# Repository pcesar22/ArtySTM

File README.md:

# ArtySTM
Artix 7 FPGA + STM32F4 Micro Board development

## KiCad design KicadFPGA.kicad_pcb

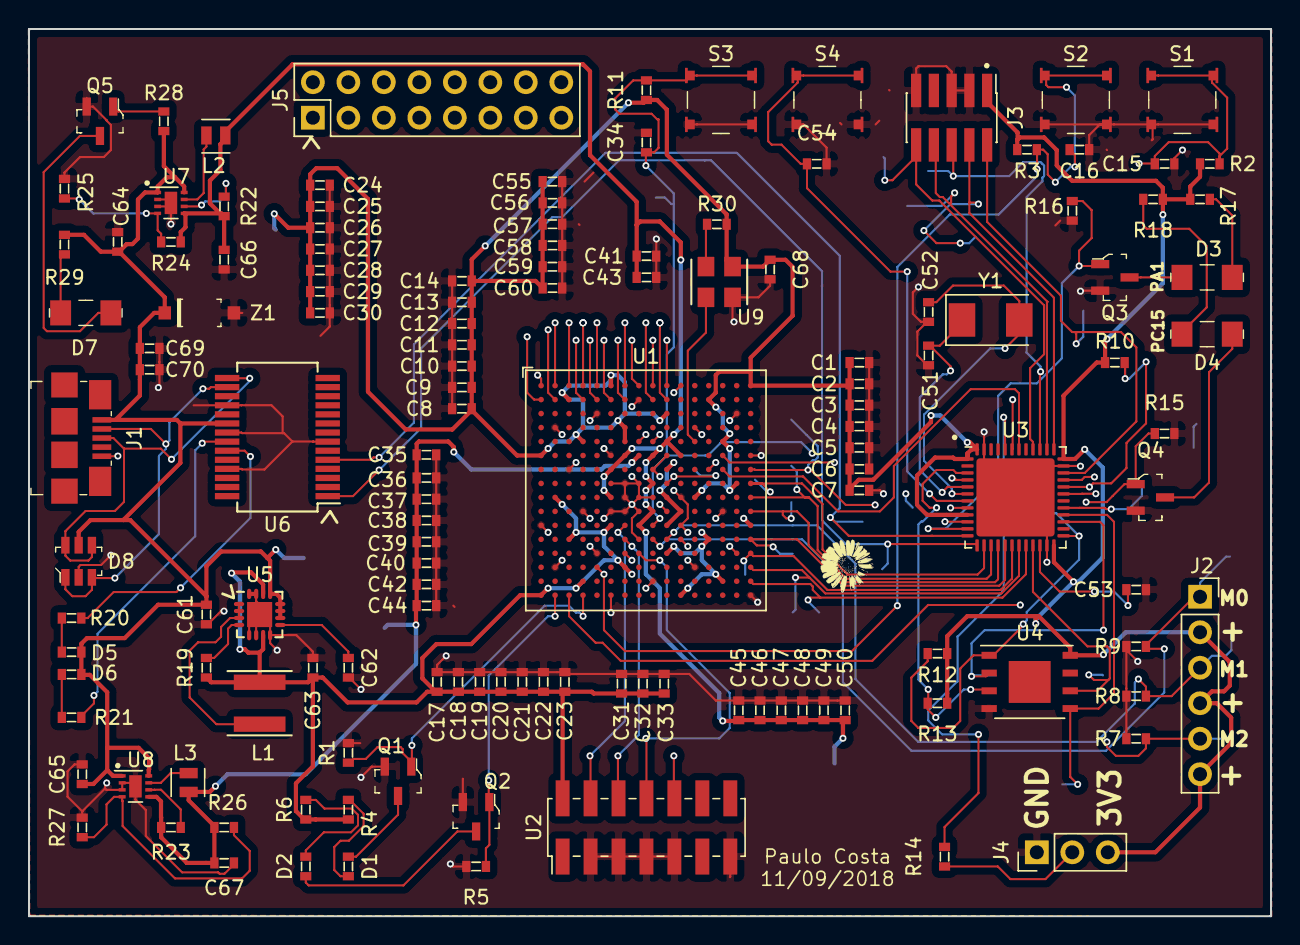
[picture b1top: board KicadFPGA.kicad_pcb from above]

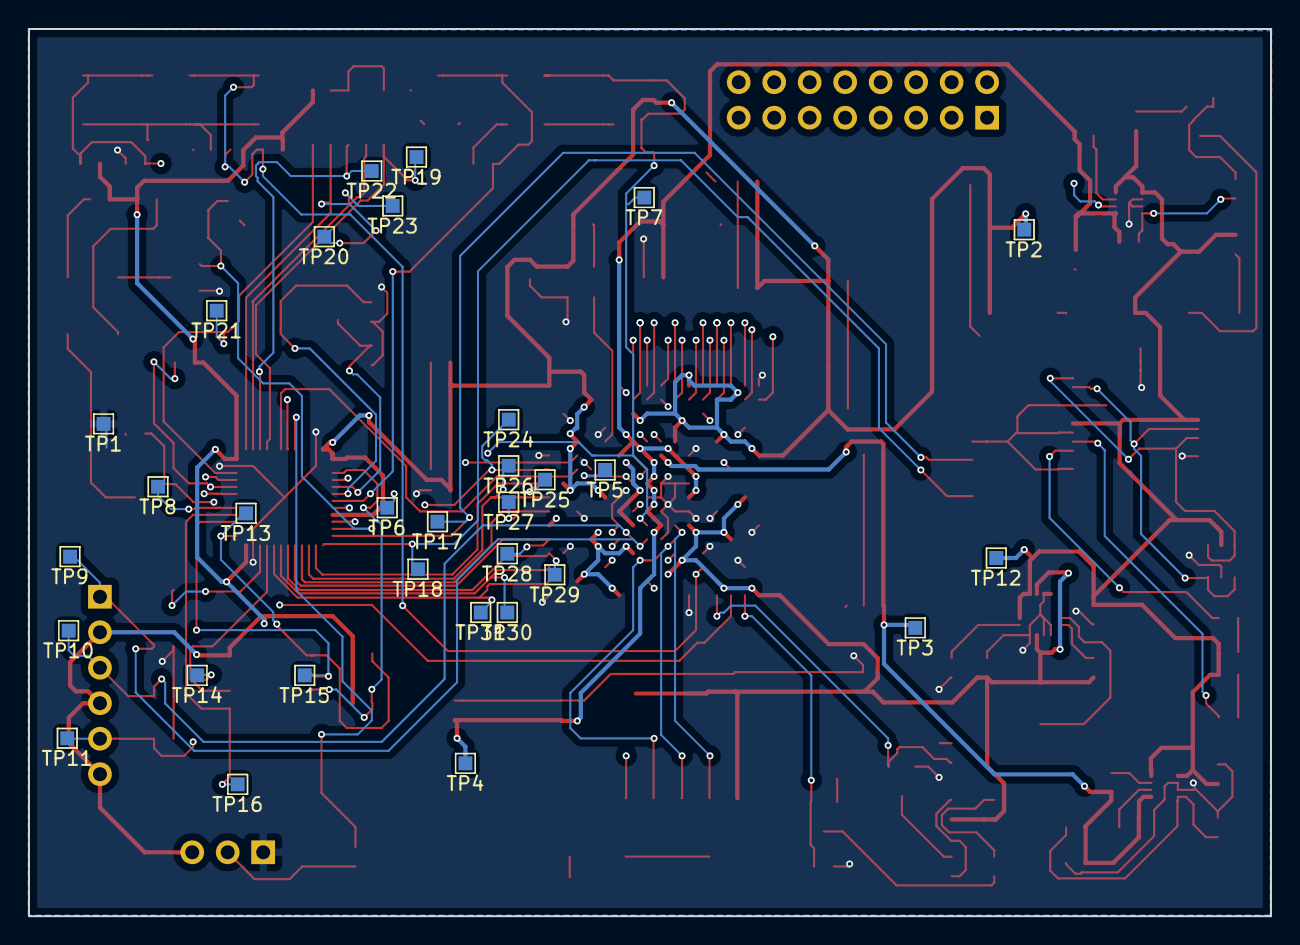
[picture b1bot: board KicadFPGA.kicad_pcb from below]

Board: 4 copper layers, 88.9 x 63.5 mm, 167 parts (31 on the bottom side), 94 nets.

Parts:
C1, C8, C17, C24, C41: 47uF; 0603
C2, C3, C9, C10, C18, C19, C25, C26, C32, C35, C36, C37, C46, C47, C53, C58, C59, C60, C69: 4.7uF; 0603
C4, C5, C6, C7, C11, C12, C13, C14, C20, C21, C22, C23, C27, C28, C29, C30, C43, C48, C49, C50: 0.47uF; 0603
C15, C16, C34, C54, C55, C56, C57, C68, C70: 0.1uF; 0603
C31, C42, C44: 47nF; 0603
C33, C38, C39, C40: 470nF; 0603
C45: 100uF; 0603
C51, C52: 8pF; 0603
C61, C64, C65: 10uF; 0603
C62: 390pF; 0603
C63, C66, C67: 22uF; 0603
D1, D2: GREEN; 0603
D3: BLUE; 1206
D4, D7: RED; 1206
D5: LED_RX; 0603
D6: LED_TX; 0603
D8: USBLC6-4SC6; SOT23-6L
J1: USB_B_Micro; USB_Micro_B_Female_10118192
J2: Conn_01x06_Male; PinSocket_1x06_P2.54mm_Vertical
J3: Conn_ARM_JTAG_SWD_10; PinHeader_2x05_P1.27mm_Vertical_SMD
J4: Conn_01x03_Male; PinHeader_1x03_P2.54mm_Vertical
J5: Conn_01x16_Male; PinHeader_2x08_P2.54mm_Vertical
L1: 2.2uH; PA4332
L2, L3: 1.0uH; L_TDK_VLF252015MT
Q1, Q2, Q3, Q4, Q5: FDV301N; SOT-23-3
R1, R5, R14, R15, R16, R28: 10k; 0603
R2, R3, R12, R13: 4.7k; 0603
R4, R6, R17, R18, R29: 680; 0603
R7, R8, R9, R30: 1k; 0603
R10, R11, R20, R21: 2.2k; 0603
R19: 100k; 0603
R22, R23: 178k; 0603
R24: 47.5k; 0603
R25, R27: 39.2k; 0603
R26: 118k; 0603
S1, S2, S3, S4: TL3315NF160Q; Switch_Tactile_SMD_4.5x4.5mm_TL3315NF160Q
TP1: tGND; TestPoint_Pad_1.0x1.0mm
TP2: t3V3; TestPoint_Pad_1.0x1.0mm
TP3: t1V8; TestPoint_Pad_1.0x1.0mm
TP4: t1V0; TestPoint_Pad_1.0x1.0mm
TP5: tFPGA_DONE; TestPoint_Pad_1.0x1.0mm
TP6: tFPGA_INIT; TestPoint_Pad_1.0x1.0mm
TP7: tFPGA_PROGRAM; TestPoint_Pad_1.0x1.0mm
TP8: tFPGA_CCLK; TestPoint_Pad_1.0x1.0mm
TP9: tFPGA_M0; TestPoint_Pad_1.0x1.0mm
TP10: tFPGA_M1; TestPoint_Pad_1.0x1.0mm
TP11: tFPGA_M2; TestPoint_Pad_1.0x1.0mm
TP12: t5V; TestPoint_Pad_1.0x1.0mm
TP13: tSPI_CS; TestPoint_Pad_1.0x1.0mm
TP14: tSPI_SCK; TestPoint_Pad_1.0x1.0mm
TP15: tSPI_MISO; TestPoint_Pad_1.0x1.0mm
TP16: tSPI_MOSI; TestPoint_Pad_1.0x1.0mm
TP17: tRXI; TestPoint_Pad_1.0x1.0mm
TP18: tTXO; TestPoint_Pad_1.0x1.0mm
TP19: tJTAG_RST; TestPoint_Pad_1.0x1.0mm
TP20: tJTAG_TCK; TestPoint_Pad_1.0x1.0mm
TP21: tJTAG_TMS; TestPoint_Pad_1.0x1.0mm
TP22: tJTAG_TDO; TestPoint_Pad_1.0x1.0mm
TP23: tJTAG_TDI; TestPoint_Pad_1.0x1.0mm
TP24: tBUS0; TestPoint_Pad_1.0x1.0mm
TP25: tBUS1; TestPoint_Pad_1.0x1.0mm
TP26: tBUS2; TestPoint_Pad_1.0x1.0mm
TP27: tBUS3; TestPoint_Pad_1.0x1.0mm
TP28: tBUS4; TestPoint_Pad_1.0x1.0mm
TP29: tBUS5; TestPoint_Pad_1.0x1.0mm
TP30: tBUS6; TestPoint_Pad_1.0x1.0mm
TP31: tBUS7; TestPoint_Pad_1.0x1.0mm
U1: XC7A35T-FTG256; BGA-256_17.0x17.0mm_Layout16x16_P1.0mm_Ball0.5mm_Pad0.4mm_N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
U2: Xilinx_FPGA_JTAG_Conn_2x7; PinHeader_2x07_P2.00mm_Vertical_SMD
U3: STM32F411CEUx; QFN-48-1EP_7x7mm_P0.5mm_EP5.6x5.6mm
U4: MT25QU128; DFN-8-1EP_6x5mm_P1.27mm_EP3x3mm
U5: TPS62142; QFN-16-1EP_3x3mm_P0.5mm_EP1.8x1.8mm
U6: FT232RL; SSOP-28_5.3x10.2mm_P0.65mm
U7, U8: TLV62084ADSGx; WSON-8-1EP_2x2mm_P0.5mm_EP0.9x1.6mm
U9: SiT8008B; SiT8008B_3.2x2.5MM
Y1: 25MHz; Crystal_SMD_Abracon_ABM3-2Pin_5.0x3.2mm
Z1: MMSZ5231B-7-F; SOD-123

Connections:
+1V0: C41.1, C43.1, C45.1, C46.1, C47.1, C48.1, C49.1, C50.1, C66.1, L2.1, R22.1, R24.1, TP4.1, U1.E10, U1.F7, U1.F9, U1.F11, U1.G6, U1.H9, U1.J6, U1.K9, U1.L8, U7.5
+1V8: C35.1, C36.1, C37.1, C38.1, C39.1, C40.1, C42.1, C44.1, C67.1, L3.1, R23.1, R26.1, TP3.1, U1.F8, U1.G10, U1.J10, U1.K11, U1.L10, U8.5
+3V3: C1.1, C2.1, C3.1, C4.1, C5.1, C6.1, C7.1, C8.1, C9.1, C10.1, C11.1, C12.1, C13.1, C14.1, C17.1, C18.1, C19.1, C20.1, C21.1, C22.1, C23.1, C24.1, C25.1, C26.1, C27.1, C28.1, C29.1, C30.1, C31.1, C32.1, C33.1, C55.1, C56.1, C57.1, C58.1, C59.1, C60.1, C63.1, C68.1, J2.2, J2.4, J2.6, J3.1, J4.3, L1.2, R2.1, R3.1, R4.1, R6.1, R10.1, R11.1, R12.1, R13.1, R17.1, R18.1, R19.1, R30.1, TP2.1, U1.A6, U1.A16, U1.B3, U1.B13, U1.C10, U1.D7, U1.E4, U1.E7, U1.E14, U1.F1, U1.H15, U1.J2, U1.J12, U1.L6, U1.L16, U1.M3, U1.M13, U1.N10, U1.P7, U1.R4, U1.R14, U1.T1, U1.T11, U2.2, U3.1, U3.9, U3.24, U3.36, U3.48, U4.8, U5.7, U5.14, U9.1
+5V: C61.1, C64.1, C65.1, C69.1, C70.1, D5.2, D6.2, D8.5, J1.1, R28.1, R29.1, TP12.1, U5.10, U5.11, U5.12, U5.13, U6.20, U7.1, U7.8, U8.1, U8.8, Z1.K
/Arty Bank 14, 15/CLK_100MHZ: U1.E12, U9.3
BOOT0: R14.2, U3.44
BREAK0: J5.1, U1.B1
BREAK1: J5.2, U1.B2
BREAK2: J5.3, U1.A2
BREAK3: J5.4, U1.A3
BREAK4: J5.5, U1.B4
BREAK5: J5.6, U1.A4
BREAK6: J5.7, U1.B5
BREAK7: J5.8, U1.A5
BREAK8: J5.9, U1.B6
BREAK9: J5.10, U1.B7
BREAK10: J5.11, U1.A7
BREAK11: J5.12, U1.A8
BREAK12: J5.13, U1.B9
BREAK13: J5.14, U1.A9
BREAK14: J5.15, U1.B10
BREAK15: J5.16, U1.A10
BUS0: TP24.1, U1.G16, U3.10
BUS1: TP25.1, U1.H16, U3.14
BUS2: TP26.1, U1.J16, U3.15
BUS3: TP27.1, U1.K16, U3.16
BUS4: TP28.1, U1.M16, U3.17
BUS5: TP29.1, U1.N16, U3.18
BUS6: TP30.1, U1.P16, U3.19
BUS7: TP31.1, U1.R16, U3.20
D+: D8.4, D8.6, J1.3, U6.15
D-: D8.1, D8.3, J1.2, U6.16
FLASH_W: R13.2, U3.3, U4.3
FPGA_BUTTON_1: C15.1, R2.2, S1.1, S1.2, U1.T3
FPGA_BUTTON_2: C16.1, R3.2, S2.1, S2.2, U1.P5
FPGA_CCLK: TP8.1, U1.E8, U3.29
FPGA_DONE: TP5.1, U1.H10, U3.33
FPGA_INIT_B: R10.2, TP6.1, U1.K10, U3.32
FPGA_LED_1: Q2.1, R5.1, U1.T2
FPGA_LED_2: Q1.1, R1.1, U1.T4
FPGA_PROGRAM_B: C34.1, R11.2, S3.1, S3.2, TP7.1, U1.L9, U3.31
FT232_RXI: TP17.1, U3.12, U6.5
FT232_TXO: TP18.1, U3.13, U6.1
GND: C1.2, C2.2, C3.2, C4.2, C5.2, C6.2, C7.2, C8.2, C9.2, C10.2, C11.2, C12.2, C13.2, C14.2, C15.2, C16.2, C17.2, C18.2, C19.2, C20.2, C21.2, C22.2, C23.2, C24.2, C25.2, C26.2, C27.2, C28.2, C29.2, C30.2, C31.2, C32.2, C33.2, C34.2, C35.2, C36.2, C37.2, C38.2, C39.2, C40.2, C41.2, C42.2, C43.2, C44.2, C45.2, C46.2, C47.2, C48.2, C49.2, C50.2, C51.2, C52.2, C53.2, C54.2, C55.2, C56.2, C57.2, C58.2, C59.2, C60.2, C61.2, C62.2, C63.2, C64.2, C65.2, C66.2, C67.2, C68.2, C69.2, C70.2, D8.2, J1.5, J3.3, J3.5, J3.9, J4.1, Q1.2, Q2.2, Q3.2, Q4.2, Q5.2, R1.2, R5.2, R7.1, R8.1, R9.1, R15.2, R16.2, R25.2, R27.2, S1.3, S1.4, S2.3, S2.4, S3.3, S3.4, S4.3, S4.4, TP1.1, U1.A1, U1.A11, U1.B8, U1.C5, U1.C15, U1.D2, U1.D12, U1.E9, U1.F6, U1.F10, U1.F16, U1.G3, U1.G9, U1.G13, U1.H6, U1.H7, U1.H8, U1.J7, U1.J8, U1.J9, U1.J11, U1.K4, U1.K6, U1.K7, U1.K8, U1.K14, U1.L1, U1.L11, U1.M8, U1.N5, U1.N15, U1.P2, U1.P12, U1.R9, U1.T6, U1.T16, U2.3, U2.5, U2.7, U2.9, U2.13, U3.8, U3.23, U3.35, U3.47, U3.49, U4.4, U5.5, U5.6, U5.8, U5.15, U5.16, U5.17, U6.7, U6.18, U6.21, U6.25, U7.2, U7.3, U7.9, U8.2, U8.3, U8.9, U9.2, Z1.A
I2C_SCL: U1.G14, U3.42
I2C_SDA: U1.F14, U3.43
M0_0: J2.1, R9.2, TP9.1, U1.M9
M1_0: J2.3, R8.2, TP10.1, U1.M10
M2_0: J2.5, R7.2, TP11.1, U1.M11
NRST: C54.1, S4.1, S4.2, U3.7
unnamed: C51.1, U3.5, Y1.1
unnamed: C52.1, U3.6, Y1.2
unnamed: C62.1, U5.9
unnamed: D1.1, Q1.3
unnamed: D1.2, R4.2
unnamed: D2.1, Q2.3
unnamed: D2.2, R6.2
unnamed: D3.1, Q3.3
unnamed: D3.2, R17.2
unnamed: D4.1, Q4.3
unnamed: D4.2, R18.2
unnamed: D5.1, R20.1
unnamed: D6.1, R21.1
unnamed: D7.1, Q5.3
unnamed: D7.2, R29.2
unnamed: J4.2, R14.1
unnamed: L1.1, U5.1, U5.2, U5.3
unnamed: L2.2, U7.7
unnamed: L3.2, U8.7
unnamed: Q5.1, R28.2
unnamed: R19.2, U5.4
unnamed: R20.2, U6.23
unnamed: R21.2, U6.22
unnamed: R22.2, U7.6
unnamed: R23.2, U8.6
unnamed: R24.2, R25.1, U7.4
unnamed: R26.2, R27.1, U8.4
unnamed: R30.2, U9.4
unnamed: U1.L7, U2.4
unnamed: U1.M7, U2.6
unnamed: U1.N7, U2.10
unnamed: U1.N8, U2.8
SPI_CS: R12.2, TP13.1, U3.25, U4.1
SPI_MISO: TP15.1, U3.27, U4.2
SPI_MOSI: TP16.1, U3.28, U4.5
SPI_SCK: TP14.1, U3.21, U4.6
STATUS_LED_GREEN: Q3.1, R16.1, U3.11
STATUS_LED_RED: Q4.1, R15.1, U3.4
STM_JTAG_RESET: J3.10, TP19.1, U3.40
STM_JTAG_TCK: J3.4, TP20.1, U3.37
STM_JTAG_TDI: J3.8, TP23.1, U3.38
STM_JTAG_TDO: J3.6, TP22.1, U3.39
STM_JTAG_TMS: J3.2, TP21.1, U3.34
VCAP1: C53.1, U3.22

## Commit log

2018-11-04 Added microcontroller and FPGA schematic entries
2018-11-07 Added power and break points. Lots of other connections. Added spi flash
2018-11-09 Placed components, now routing
2018-11-10 finished routing the thing
2018-11-10 Adding custom library files
